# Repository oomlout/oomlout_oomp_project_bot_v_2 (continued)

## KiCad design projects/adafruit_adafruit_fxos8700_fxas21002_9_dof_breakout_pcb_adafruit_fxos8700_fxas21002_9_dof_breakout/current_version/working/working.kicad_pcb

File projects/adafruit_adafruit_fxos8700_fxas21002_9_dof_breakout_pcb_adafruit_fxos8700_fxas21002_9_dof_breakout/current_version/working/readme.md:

# adafruit_fxos8700_fxas21002_9_dof_breakout_pcb
 
## summary 
* id: adafruit_adafruit_fxos8700_fxas21002_9_dof_breakout_pcb_adafruit_fxos8700_fxas21002_9_dof_breakout
* user: adafruit
* name: adafruit_fxos8700_fxas21002_9_dof_breakout_pcb
* board: adafruit_fxos8700_fxas21002_9_dof_breakout
* repo: https://github.com/adafruit/Adafruit-FXOS8700-FXAS21002-9-DoF-Breakout-PCB

* src_file_repo_sch: 
* src_file_repo_sch_link: https://github.com/adafruit/Adafruit-FXOS8700-FXAS21002-9-DoF-Breakout-PCB/tree/master/
* full details link: https://github.com/oomlout/oomlout_oomp_project_bot_v_2/tree/main/projects/adafruit_adafruit_fxos8700_fxas21002_9_dof_breakout_pcb_adafruit_fxos8700_fxas21002_9_dof_breakout/current_version/working  

## schematic  
  
[schematic (pdf)](working_schematic.pdf) 

## pcb  

[board (pdf)](working.pdf)  

## working_bom
| Id | Designator | Footprint | Quantity | Designation | Supplier and ref |  | None | 
| --- | --- | --- | --- | --- | --- | --- | --- | 
| 1 | U$28 | SYMBOL_GYRO_CLOCKWISE | 1 |  |  |  | [''] | 
| 2 | U$27 | SYMBOL_GYRO_CCLOCKWISE | 1 |  |  |  | [''] | 
| 3 | U$1,U$3,U$4,U$2 | MOUNTINGHOLE_2.5_PLATED | 4 | MOUNTINGHOLE2.5 |  |  | [''] | 
| 4 | U1 | SOT23-5 | 1 | MIC5225-3.3V |  |  | [''] | 
| 5 | JP2 | 1X04_ROUND | 1 |  |  |  | [''] | 
| 6 | C2,C3,C7,C5 | 0805-NO | 4 | 0.1uF |  |  | [''] | 
| 7 | C4 | 0805-NO | 1 | 10uF |  |  | [''] | 
| 8 | FID3,FID2,FID1 | FIDUCIAL_1MM | 3 | FIDUCIAL_1MM |  |  | [''] | 
| 9 | JP1 | 1X06_ROUND_70 | 1 |  |  |  | [''] | 
| 10 | R6,R1,R5,R2,R3,R4 | 0805-NO | 6 | 10K |  |  | [''] | 
| 11 | D1 | SOD-323 | 1 | 1N4148 |  |  | [''] | 
| 12 | Q3,Q2,Q1 | SOT23-WIDE | 3 | BSS138 |  |  | [''] | 
| 13 | U$26 | ADAFRUIT_2.5MM | 1 |  |  |  | [''] | 
| 14 | C6,C1 | 0805-NO | 2 | 10ÂµF |  |  | [''] | 
| 15 | U$31 | SYMBOL_GYRO_Z | 1 |  |  |  | [''] | 
| 16 | U2 | QFN16_3MM_FREESCALE_5X3 | 1 | FXOS8700CQ |  |  | [''] | 
| 17 | U4 | QFN24_4MM_FREESCALE_7X5 | 1 | FXAS21002C |  |  | [''] | 
| 18 | U$32 | PCBFEAT-REV-040 | 1 |  |  |  | [''] | 

## bom_schematic
| Ref | Qnty | Value | Cmp name | Footprint | Description | Vendor | DNP | 
| --- | --- | --- | --- | --- | --- | --- | --- | 
| C1, C6 | 2 | 10ÂµF | CAP_CERAMIC0805-NOOUTLINE | working:0805-NO |  |  |  | 
| C2, C3, C5, C7 | 4 | 0.1uF | CAP_CERAMIC0805-NOOUTLINE | working:0805-NO |  |  |  | 
| C4 | 1 | 10uF | CAP_CERAMIC0805-NOOUTLINE | working:0805-NO |  |  |  | 
| D1 | 1 | 1N4148 | DIODESOD-323 | working:SOD-323 |  |  |  | 
| FID1, FID2, FID3 | 3 | FIDUCIAL_1MM | FIDUCIAL_1MM | working:FIDUCIAL_1MM |  |  |  | 
| JP1 | 1 | HEADER-1X670MIL | HEADER-1X670MIL | working:1X06_ROUND_70 |  |  |  | 
| JP2 | 1 | HEADER-1X4ROUND | HEADER-1X4ROUND | working:1X04_ROUND |  |  |  | 
| Q1, Q2, Q3 | 3 | BSS138 | MOSFET-NWIDE | working:SOT23-WIDE |  |  |  | 
| R1, R2, R3, R4, R5, R6 | 6 | 10K | RESISTOR0805_NOOUTLINE | working:0805-NO |  |  |  | 
| U1 | 1 | MIC5225-3.3V | VREG_SOT23-5 | working:SOT23-5 |  |  |  | 
| U2 | 1 | FXOS8700CQ | ACCEL_MAG_FXOS8700CQ | working:QFN16_3MM_FREESCALE_5X3 |  |  |  | 
| U4 | 1 | FXAS21002C | GYRO_FXAS21002C | working:QFN24_4MM_FREESCALE_7X5 |  |  |  | 
| U$1, U$2, U$3, U$4 | 4 | MOUNTINGHOLE2.5 | MOUNTINGHOLE2.5 | working:MOUNTINGHOLE_2.5_PLATED |  |  |  | 

## mounting_holes
| x | y | package | value | ref | size | 
| --- | --- | --- | --- | --- | --- | 
| 22.86 | 0.0 | MOUNTINGHOLE_2.5_PLATED | MOUNTINGHOLE2.5 | U$1 | m3 | 
| 0.0 | 15.24 | MOUNTINGHOLE_2.5_PLATED | MOUNTINGHOLE2.5 | U$2 | m3 | 
| 22.86 | 15.24 | MOUNTINGHOLE_2.5_PLATED | MOUNTINGHOLE2.5 | U$3 | m3 | 
| 0.0 | 0.0 | MOUNTINGHOLE_2.5_PLATED | MOUNTINGHOLE2.5 | U$4 | m3 |

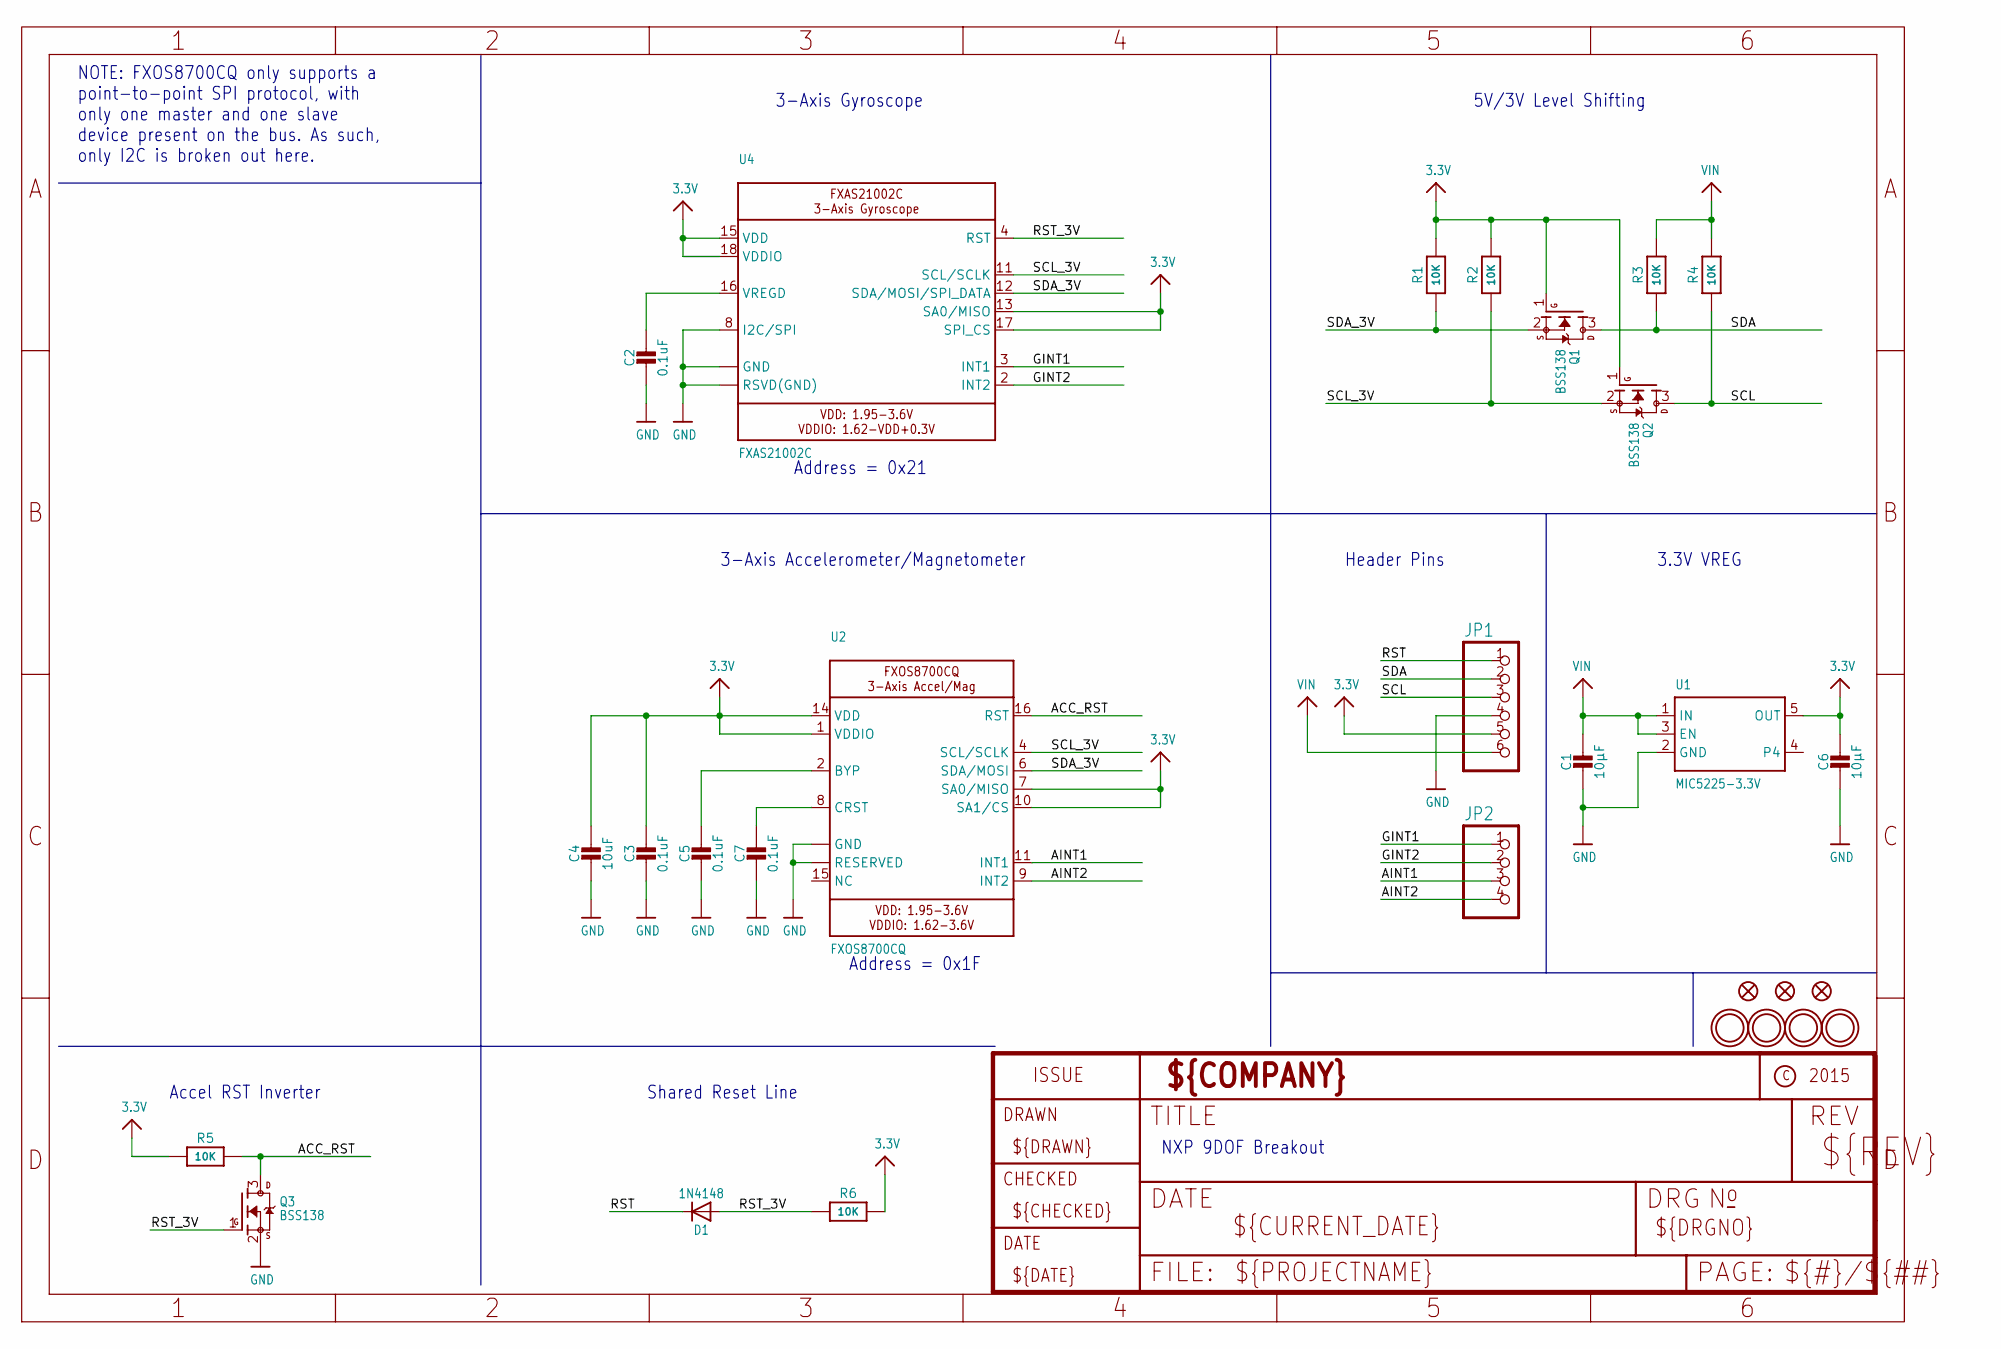
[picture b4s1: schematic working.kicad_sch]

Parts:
C1, C6: 10µF; 0805-NO
C2, C3, C5, C7: 0.1uF; 0805-NO
C4: 10uF; 0805-NO
D1: 1N4148; SOD-323
FID1, FID2, FID3: FIDUCIAL_1MM
JP1: HEADER-1X670MIL; 1X06_ROUND_70
JP2: HEADER-1X4ROUND; 1X04_ROUND
Q1, Q2, Q3: BSS138; SOT23-WIDE
R1, R2, R3, R4, R5, R6: 10K; 0805-NO
U1: MIC5225-3.3V; SOT23-5
U2: FXOS8700CQ; QFN16_3MM_FREESCALE_5X3
U4: FXAS21002C; QFN24_4MM_FREESCALE_7X5
U$1, U$2, U$3, U$4: MOUNTINGHOLE2.5; MOUNTINGHOLE_2.5_PLATED

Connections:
3.3V: C3.1, C4.1, C6.1, JP1.5, Q1.1 (G), Q2.1 (G), R1.2, R2.2, R5.1, R6.2, U1.5 (OUT), U2.1 (VDDIO), U2.7 (SA0/MISO), U2.10 (SA1/CS), U2.14 (VDD), U4.13 (SA0/MISO), U4.15 (VDD), U4.17 (SPI_CS), U4.18 (VDDIO)
ACC_RST: Q3.3 (D), R5.2, U2.16 (RST)
AINT1: JP2.3, U2.11 (INT1)
AINT2: JP2.4, U2.9 (INT2)
GINT1: JP2.1, U4.3 (INT1)
GINT2: JP2.2, U4.2 (INT2)
GND: C1.2, C2.2, C3.2, C4.2, C5.2, C6.2, C7.2, JP1.4, Q3.2 (S), U1.2 (GND), U2.3 (RESERVED), U2.5 (GND), U2.12 (GND), U2.13 (RESERVED), U4.1 (GND), U4.5 (GND), U4.6 (RSVD(GND)), U4.7 (RSVD(GND)), U4.8 (I2C/SPI), U4.9 (RSVD(GND)), U4.10 (RSVD(GND)), U4.14 (GND), U4.19 (GND), U4.20 (RSVD(GND)), U4.21 (RSVD(GND)), U4.22 (RSVD(GND)), U4.23 (RSVD(GND)), U4.24 (RSVD(GND))
unnamed: C2.1, U4.16 (VREGD)
unnamed: C5.1, U2.2 (BYP)
unnamed: C7.1, U2.8 (CRST)
RST: D1.C, JP1.1
RST_3V: D1.A, Q3.1 (G), R6.1, U4.4 (RST)
SCL: JP1.3, Q2.3 (D), R4.1
SCL_3V: Q2.2 (S), R2.1, U2.4 (SCL/SCLK), U4.11 (SCL/SCLK)
SDA: JP1.2, Q1.3 (D), R3.1
SDA_3V: Q1.2 (S), R1.1, U2.6 (SDA/MOSI), U4.12 (SDA/MOSI/SPI_DATA)
VIN: C1.1, JP1.6, R3.2, R4.2, U1.1 (IN), U1.3 (EN)

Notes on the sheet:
Address = 0x21
3-Axis Gyroscope
Address = 0x1F
3-Axis Accelerometer/Magnetometer
Accel RST Inverter
Shared Reset Line
NOTE: FXOS8700CQ only supports a point-to-point SPI protocol, with only one master and one slave device present on the bus. As such, only I2C is broken out here.
Header Pins
5V/3V Level Shifting
NXP 9DOF Breakout
3.3V VREG

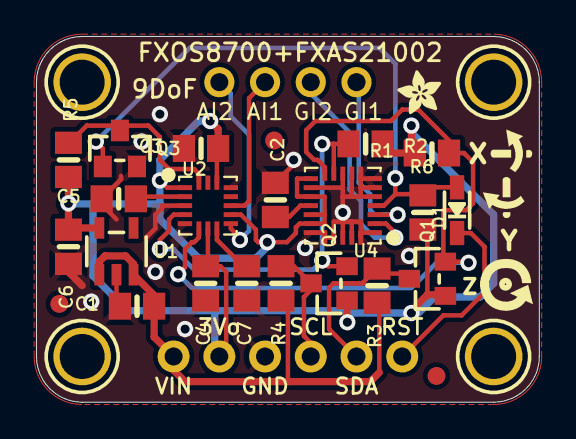
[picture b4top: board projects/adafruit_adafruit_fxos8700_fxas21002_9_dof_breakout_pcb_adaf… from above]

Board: 2 copper layers, 27.9 x 20.3 mm, 34 parts (1 on the bottom side), 17 nets.

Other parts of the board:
U$26: ADAFRUIT_2.5MM
U$27: SYMBOL_GYRO_CCLOCKWISE
U$28: SYMBOL_GYRO_CLOCKWISE
U$31: SYMBOL_GYRO_Z
U$32: PCBFEAT-REV-040

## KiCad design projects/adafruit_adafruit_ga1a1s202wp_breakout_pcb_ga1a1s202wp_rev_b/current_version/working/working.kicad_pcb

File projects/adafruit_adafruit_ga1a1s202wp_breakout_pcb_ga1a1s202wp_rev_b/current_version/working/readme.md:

# adafruit_ga1a1s202wp_breakout_pcb
 
## summary 
* id: adafruit_adafruit_ga1a1s202wp_breakout_pcb_ga1a1s202wp_rev_b
* user: adafruit
* name: adafruit_ga1a1s202wp_breakout_pcb
* board: ga1a1s202wp_rev_b
* repo: https://github.com/adafruit/Adafruit-GA1A1S202WP-Breakout-PCB

* src_file_repo_sch: 
* src_file_repo_sch_link: https://github.com/adafruit/Adafruit-GA1A1S202WP-Breakout-PCB/tree/master/
* full details link: https://github.com/oomlout/oomlout_oomp_project_bot_v_2/tree/main/projects/adafruit_adafruit_ga1a1s202wp_breakout_pcb_ga1a1s202wp_rev_b/current_version/working  

## schematic  
  
[schematic (pdf)](working_schematic.pdf) 

## pcb  

[board (pdf)](working.pdf)  

## working_bom
| Id | Designator | Footprint | Quantity | Designation | Supplier and ref |  | None | 
| --- | --- | --- | --- | --- | --- | --- | --- | 
| 1 | FID1,FID2 | FIDUCIAL_1MM | 2 | FIDUCIAL" |  |  | [''] | 
| 2 | U$3 | MOUNTINGHOLE_2.5_PLATED | 1 | MOUNTINGHOLE2.5 |  |  | [''] | 
| 3 | U$4 | ADAFRUIT_2.5MM | 1 |  |  |  | [''] | 
| 4 | C1 | _0805MP | 1 | 0.1uF |  |  | [''] | 
| 5 | JP1 | 1X03_ROUND | 1 |  |  |  | [''] | 
| 6 | U1 | GA1A1S202WP | 1 | GA1A1S202WP |  |  | [''] | 
| 7 | R1 | _0805MP | 1 | 68K |  |  | [''] | 

## bom_schematic
| Ref | Qnty | Value | Cmp name | Footprint | Description | Vendor | DNP | 
| --- | --- | --- | --- | --- | --- | --- | --- | 
| C1 | 1 | 0.1uF | CAP_CERAMIC_0805MP | working:_0805MP |  |  |  | 
| FID1, FID2 | 2 | FIDUCIAL"" | FIDUCIAL{dblquote}{dblquote} | working:FIDUCIAL_1MM |  |  |  | 
| JP1 | 1 | HEADER-1X3ROUND | HEADER-1X3ROUND | working:1X03_ROUND |  |  |  | 
| R1 | 1 | 68K | RESISTOR_0805MP | working:_0805MP |  |  |  | 
| U1 | 1 | GA1A1S202WP | GA1A1S202WP | working:GA1A1S202WP |  |  |  | 
| U$3 | 1 | MOUNTINGHOLE2.5 | MOUNTINGHOLE2.5 | working:MOUNTINGHOLE_2.5_PLATED |  |  |  | 

## mounting_holes
| x | y | package | value | ref | size | 
| --- | --- | --- | --- | --- | --- | 
| 0.0 | 0.0 | MOUNTINGHOLE_2.5_PLATED | MOUNTINGHOLE2.5 | U$3 | m3 |

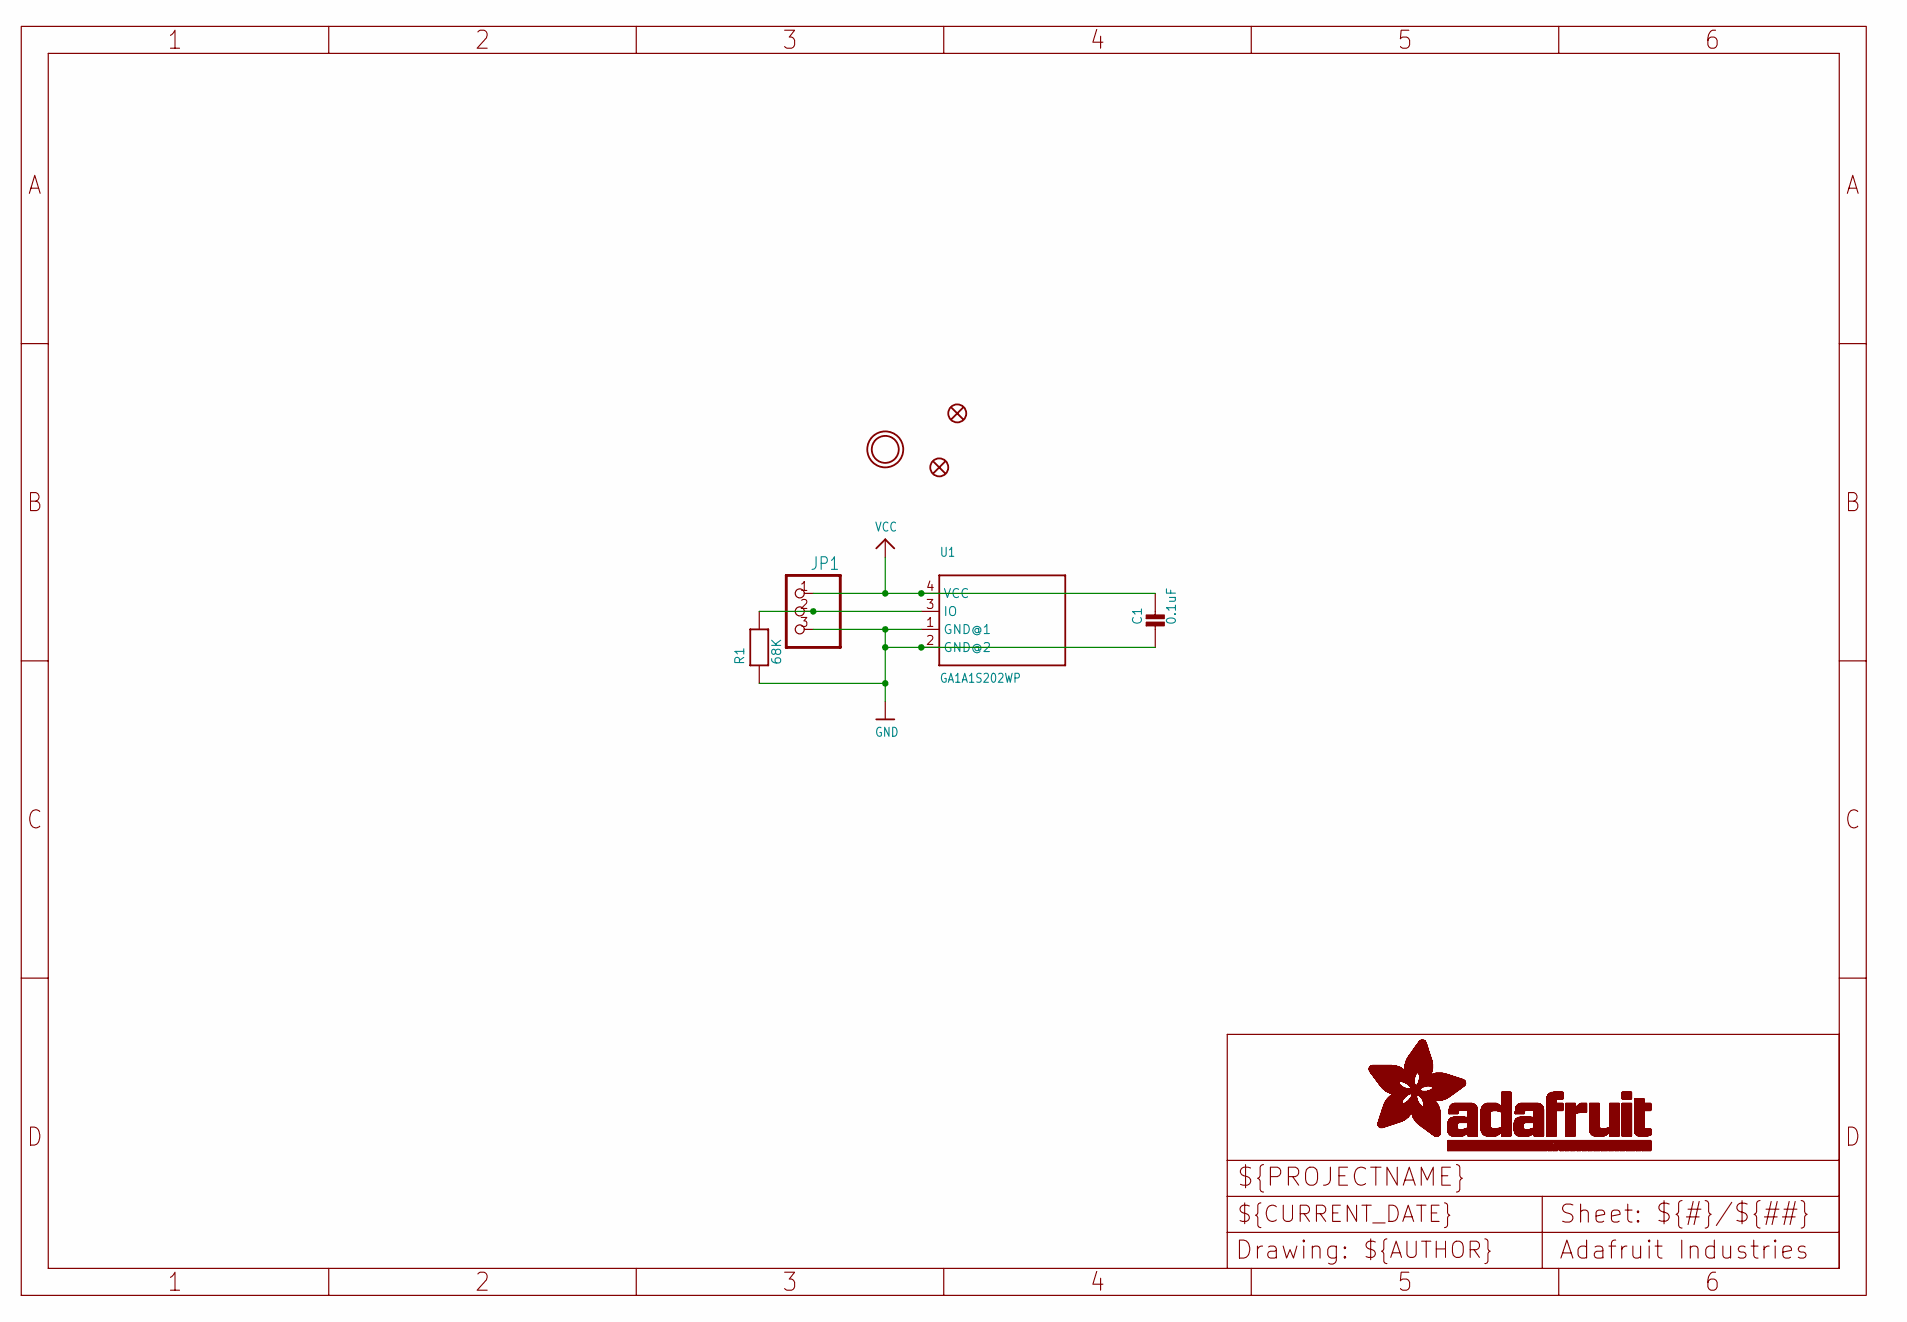
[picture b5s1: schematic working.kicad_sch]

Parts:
C1: 0.1uF; _0805MP
FID1, FID2: FIDUCIAL""; FIDUCIAL_1MM
JP1: HEADER-1X3ROUND; 1X03_ROUND
R1: 68K; _0805MP
U1: GA1A1S202WP
U$3: MOUNTINGHOLE2.5; MOUNTINGHOLE_2.5_PLATED

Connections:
GND: C1.2, JP1.3, R1.1, U1.1 (GND@1), U1.2 (GND@2)
unnamed: JP1.2, R1.2, U1.3 (IO)
VCC: C1.1, JP1.1, U1.4 (VCC)

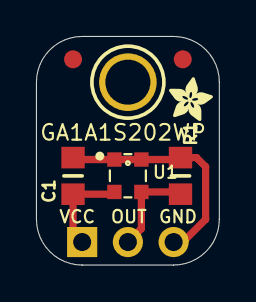
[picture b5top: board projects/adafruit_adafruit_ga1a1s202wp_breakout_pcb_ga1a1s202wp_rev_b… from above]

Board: 2 copper layers, 10.2 x 12.7 mm, 8 parts (0 on the bottom side), 3 nets.

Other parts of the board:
U$4: ADAFRUIT_2.5MM

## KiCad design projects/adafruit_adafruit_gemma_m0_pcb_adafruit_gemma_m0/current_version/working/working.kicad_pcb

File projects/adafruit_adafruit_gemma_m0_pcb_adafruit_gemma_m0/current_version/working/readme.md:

# adafruit_gemma_m0_pcb
 
## summary 
* id: adafruit_adafruit_gemma_m0_pcb_adafruit_gemma_m0
* user: adafruit
* name: adafruit_gemma_m0_pcb
* board: adafruit_gemma_m0
* repo: https://github.com/adafruit/Adafruit-Gemma-M0-PCB

* src_file_repo_sch: 
* src_file_repo_sch_link: https://github.com/adafruit/Adafruit-Gemma-M0-PCB/tree/master/
* full details link: https://github.com/oomlout/oomlout_oomp_project_bot_v_2/tree/main/projects/adafruit_adafruit_gemma_m0_pcb_adafruit_gemma_m0/current_version/working  

## schematic  
  
[schematic (pdf)](working_schematic.pdf) 

## pcb  

[board (pdf)](working.pdf)  

## working_bom
| Id | Designator | Footprint | Quantity | Designation | Supplier and ref |  | None | 
| --- | --- | --- | --- | --- | --- | --- | --- | 
| 1 | GND0,UNK3V3,B1,B2,B0,VBAT0 | SEWALLI | 6 | SEWTAP-ALLIGATOR |  |  | [''] | 
| 2 | SW1 | EG1390 | 1 | EG1218 |  |  | [''] | 
| 3 | U$1,U$6 | FIDUCIAL_1MM | 2 | FIDUCIAL_1MM |  |  | [''] | 
| 4 | C2,C3 | 0603-NO | 2 | 1uF |  |  | [''] | 
| 5 | C8,C1 | 0805-NO | 2 | 10uF |  |  | [''] | 
| 6 | D1,D2 | SOD-123FL | 2 | SCHOTTKY |  |  | [''] | 
| 7 | R5 | 0603-NO | 1 | 1K |  |  | [''] | 
| 8 | PWR0 | CHIPLED_0603_NOOUTLINE | 1 | red |  |  | [''] | 
| 9 | CN1 | JSTPH2 | 1 | JST-PH |  |  | [''] | 
| 10 | LED1 | APA102_2020 | 1 | AP102-2020 |  |  | [''] | 
| 11 | IC1 | QFN32_5MM | 1 | ATSAMD21E |  |  | [''] | 
| 12 | Q1 | BTN_KMR2_4.6X2.8 | 1 | reset |  |  | [''] | 
| 13 | X2 | 4UCONN_20329_V2 | 1 | MicroUSB |  |  | [''] | 
| 14 | U$8 | GEMMA_M0_TOP | 1 |  |  |  | [''] | 
| 15 | U1 | SOT23-5 | 1 | AP2112K-3.3 |  |  | [''] | 
| 16 | TP1 | TP16R | 1 | TPTP16R |  |  | [''] | 
| 17 | SWD0,SWC0 | TP15R | 2 | TPTP15R |  |  | [''] | 
| 18 | U$10 | PCBFEAT-REV-040 | 1 |  |  |  | [''] | 
| 19 | U$7 | GEMMA_M0_BOTTOM | 1 |  |  |  | [''] | 

## bom_schematic
| Ref | Qnty | Value | Cmp name | Footprint | Description | Vendor | DNP | 
| --- | --- | --- | --- | --- | --- | --- | --- | 
| B0, B1, B2 | 3 | SEWTAP-ALLIGATOR | SEWTAP-ALLIGATOR | working:SEWALLI |  |  |  | 
| C1, C8 | 2 | 10uF | CAP_CERAMIC0805-NOOUTLINE | working:0805-NO |  |  |  | 
| C2, C3 | 2 | 1uF | CAP_CERAMIC0603_NO | working:0603-NO |  |  |  | 
| CN1 | 1 | JST-PH | CON_JST_PH_2PIN | working:JSTPH2 |  |  |  | 
| D1, D2 | 2 | SCHOTTKY | DIODE_SOD-123FL | working:SOD-123FL |  |  |  | 
| GND0 | 1 | SEWTAP-ALLIGATOR | SEWTAP-ALLIGATOR | working:SEWALLI |  |  |  | 
| IC1 | 1 | ATSAMD21E | ATSAMD21E | working:QFN32_5MM |  |  |  | 
| LED1 | 1 | AP102-2020 | APA1022020 | working:APA102_2020 |  |  |  | 
| PWR0 | 1 | red | LED0603_NOOUTLINE | working:CHIPLED_0603_NOOUTLINE |  |  |  | 
| Q1 | 1 | reset | SWITCH_TACT_SMT4.6X2.8 | working:BTN_KMR2_4.6X2.8 |  |  |  | 
| R5 | 1 | 1K | RESISTOR_0603_NOOUT | working:0603-NO |  |  |  | 
| SW1 | 1 | EG1218 | SWITCH_DPDTEG1390 | working:EG1390 |  |  |  | 
| SWC0 | 1 | TPTP15R | TPTP15R | working:TP15R |  |  |  | 
| SWD0 | 1 | TPTP15R | TPTP15R | working:TP15R |  |  |  | 
| TP1 | 1 | TPTP16R | TPTP16R | working:TP16R |  |  |  | 
| U1 | 1 | AP2112K-3.3 | VREG_SOT23-5 | working:SOT23-5 |  |  |  | 
| U$1, U$6 | 2 | FIDUCIAL_1MM | FIDUCIAL_1MM | working:FIDUCIAL_1MM |  |  |  | 
| UNK3V3 | 1 | SEWTAP-ALLIGATOR | SEWTAP-ALLIGATOR | working:SEWALLI |  |  |  | 
| VBAT0 | 1 | SEWTAP-ALLIGATOR | SEWTAP-ALLIGATOR | working:SEWALLI |  |  |  | 
| X2 | 1 | MicroUSB | USB_MICRO_20329_V2 | working:4UCONN_20329_V2 |  |  |  |

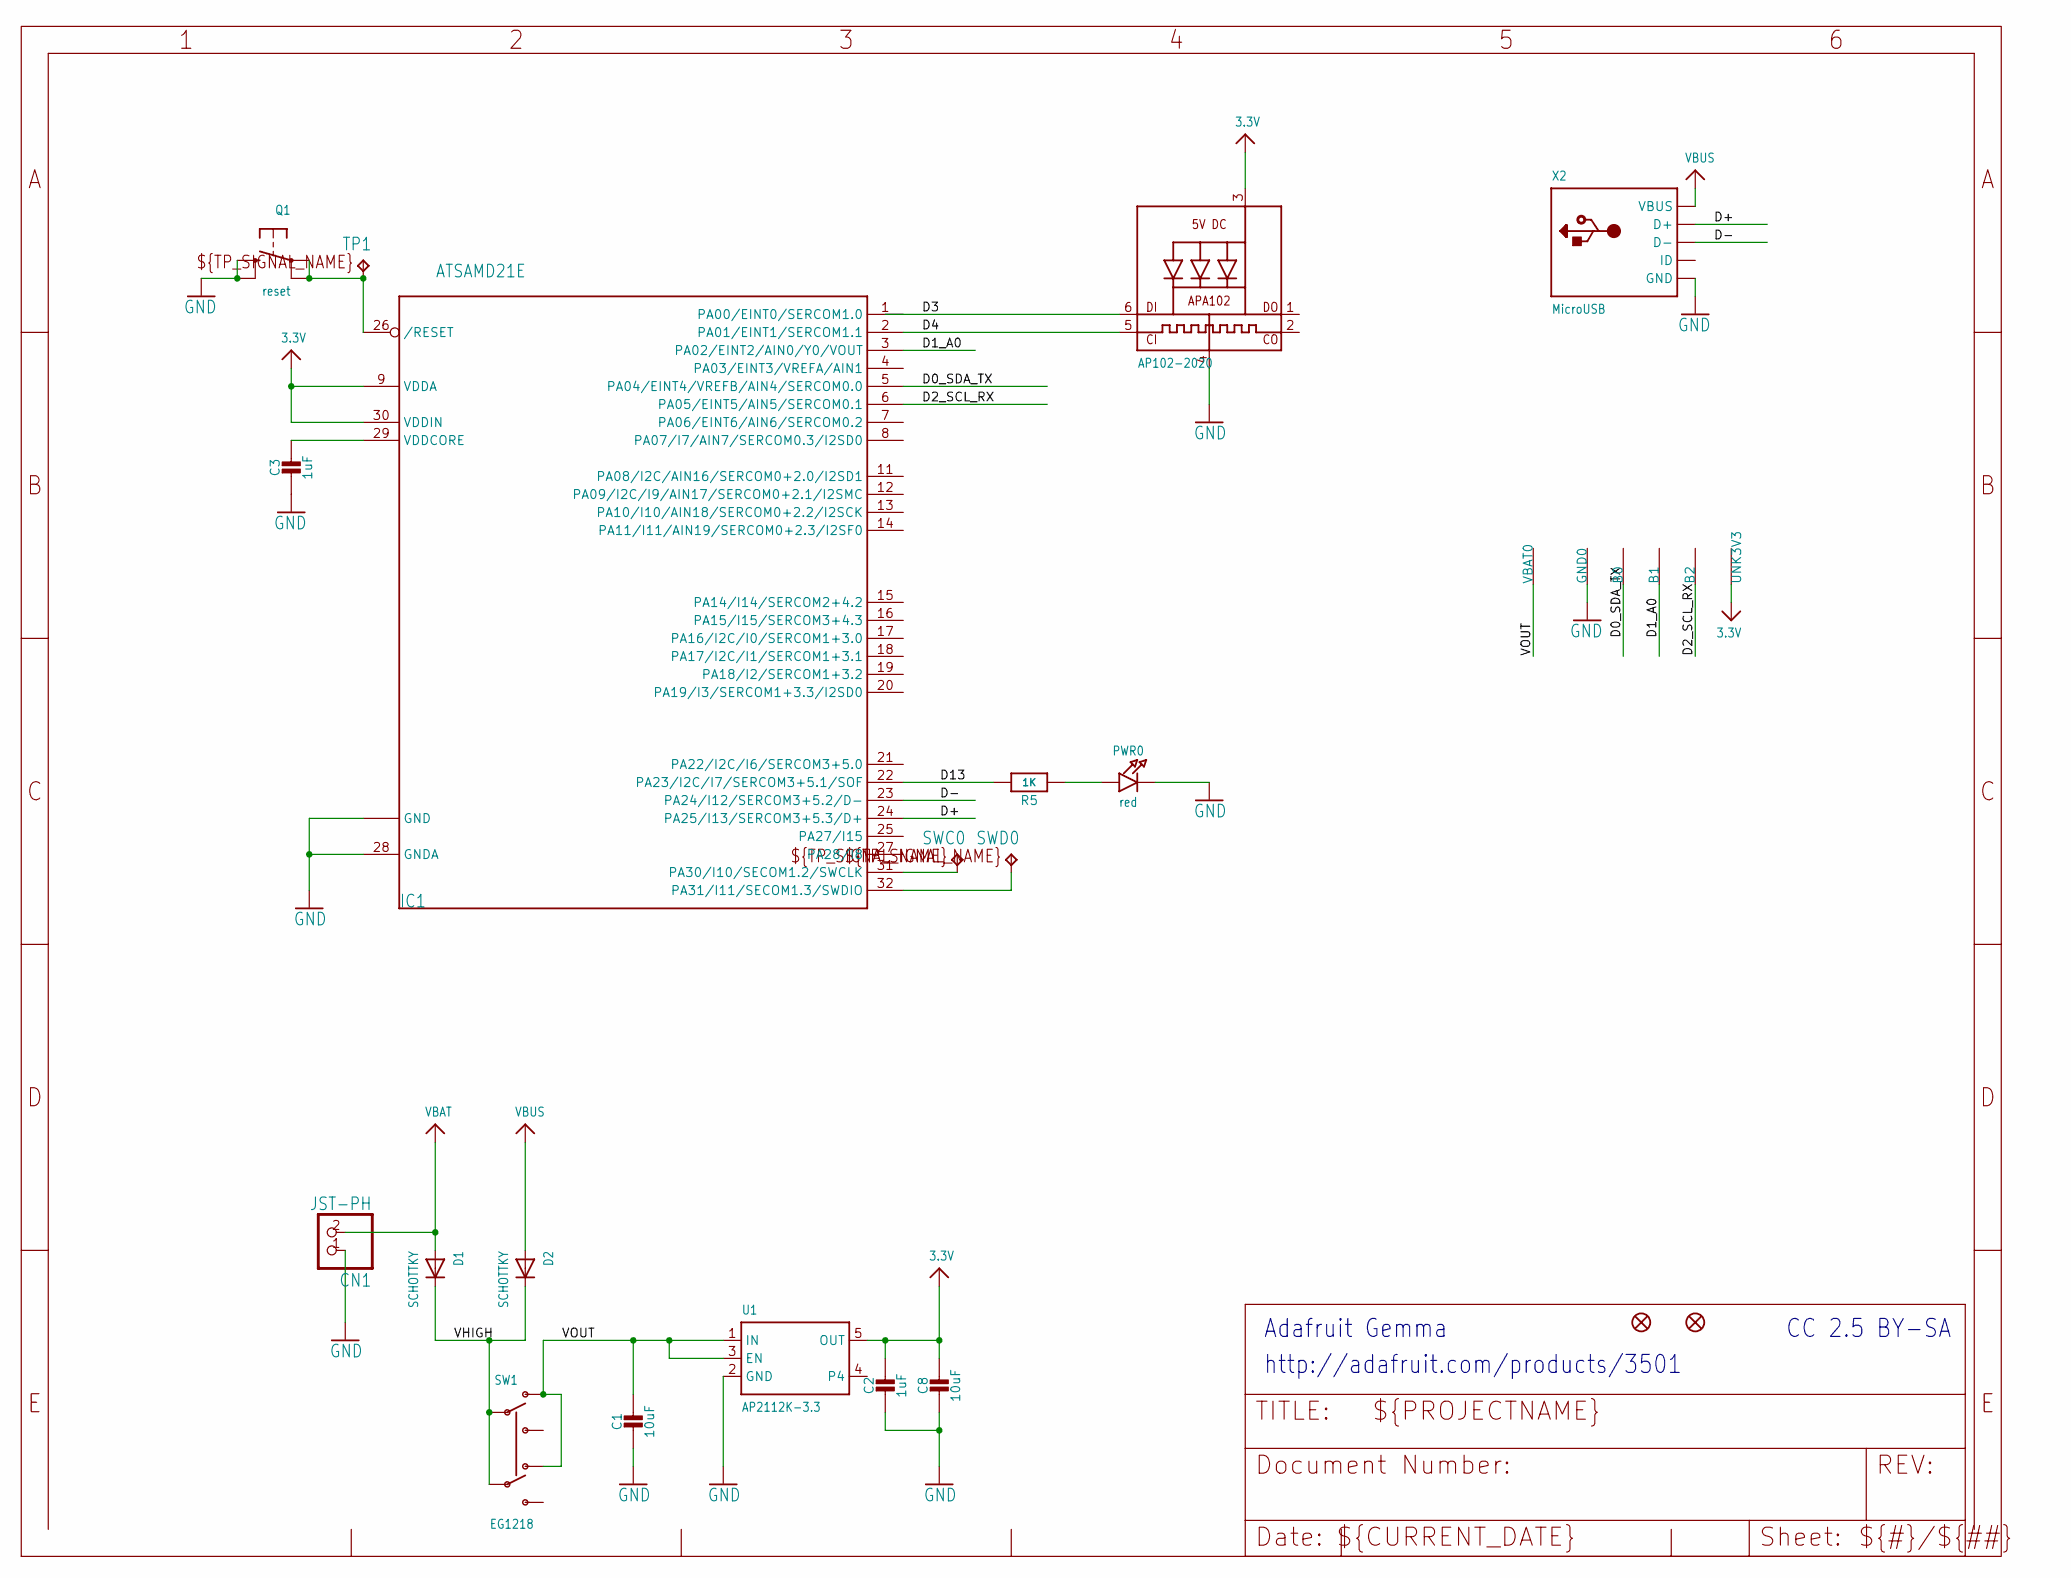
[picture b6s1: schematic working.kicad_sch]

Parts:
B0, B1, B2: SEWTAP-ALLIGATOR; SEWALLI
C1, C8: 10uF; 0805-NO
C2, C3: 1uF; 0603-NO
CN1: JST-PH; JSTPH2
D1, D2: SCHOTTKY; SOD-123FL
GND0: SEWTAP-ALLIGATOR; SEWALLI
IC1: ATSAMD21E; QFN32_5MM
LED1: AP102-2020; APA102_2020
PWR0: red; CHIPLED_0603_NOOUTLINE
Q1: reset; BTN_KMR2_4.6X2.8
R5: 1K; 0603-NO
SW1: EG1218; EG1390
SWC0: TPTP15R; TP15R
SWD0: TPTP15R; TP15R
TP1: TPTP16R; TP16R
U1: AP2112K-3.3; SOT23-5
U$1, U$6: FIDUCIAL_1MM
UNK3V3: SEWTAP-ALLIGATOR; SEWALLI
VBAT0: SEWTAP-ALLIGATOR; SEWALLI
X2: MicroUSB; 4UCONN_20329_V2

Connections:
3.3V: C2.1, C8.1, IC1.9 (VDDA), IC1.30 (VDDIN), LED1.3 (VDD), U1.5 (OUT), UNK3V3.P$1
D0_SDA_TX: B0.P$1, IC1.5 (PA04/EINT4/VREFB/AIN4/SERCOM0.0)
D1_A0: B1.P$1, IC1.3 (PA02/EINT2/AIN0/Y0/VOUT)
D2_SCL_RX: B2.P$1, IC1.6 (PA05/EINT5/AIN5/SERCOM0.1)
D3: IC1.1 (PA00/EINT0/SERCOM1.0), LED1.6 (DI)
D4: IC1.2 (PA01/EINT1/SERCOM1.1), LED1.5 (CKI)
D13: IC1.22 (PA23/I2C/I7/SERCOM3+5.1/SOF), R5.2
D+: IC1.24 (PA25/I13/SERCOM3+5.3/D+), X2.D+
D-: IC1.23 (PA24/I12/SERCOM3+5.2/D-), X2.D-
GND: C1.2, C2.2, C3.2, C8.2, CN1.1, GND0.P$1, IC1.10 (GND), IC1.28 (GNDA), IC1.33 (GND), LED1.4 (GND), PWR0.C, Q1.B (S), Q1.B' (S1), U1.2 (GND), X2.BASE@1 (GND), X2.BASE@2 (GND), X2.GND, X2.SPRT@1 (GND), X2.SPRT@2 (GND), X2.SPRT@3 (GND), X2.SPRT@4 (GND)
unnamed: PWR0.A, R5.1
SWCLK: IC1.31 (PA30/I10/SECOM1.2/SWCLK), SWC0.TP
SWDIO: IC1.32 (PA31/I11/SECOM1.3/SWDIO), SWD0.TP
VBAT: CN1.2, D1.A
VBUS: D2.A, X2.VBUS
VDDCORE: C3.1, IC1.29 (VDDCORE)
VHIGH: D1.C, D2.C, SW1.P1, SW1.P2
VOUT: C1.1, SW1.O1, SW1.O2, U1.1 (IN), U1.3 (EN), VBAT0.P$1
~RESET: IC1.26 (/RESET), Q1.A, Q1.A' (P1), TP1.TP

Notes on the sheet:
Adafruit Gemma
http://adafruit.com/products/3501
CC 2.5 BY-SA

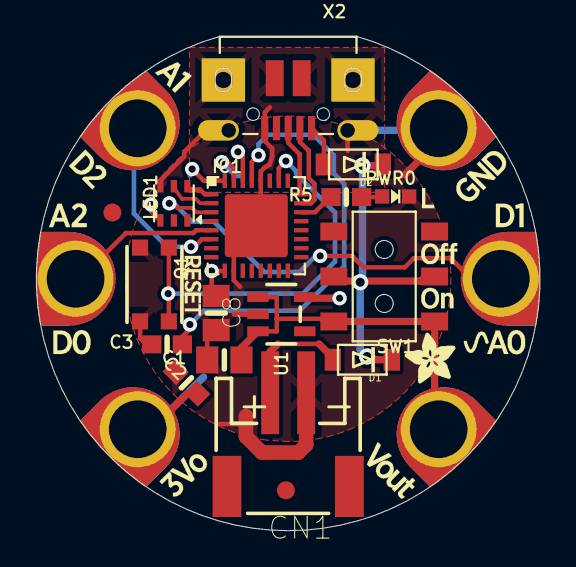
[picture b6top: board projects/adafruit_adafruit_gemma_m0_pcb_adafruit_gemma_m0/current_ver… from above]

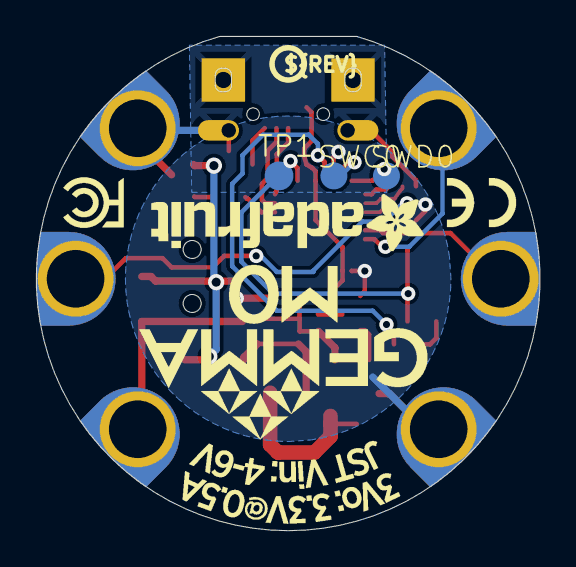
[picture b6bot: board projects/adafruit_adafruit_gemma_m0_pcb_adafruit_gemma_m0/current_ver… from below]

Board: 16 copper layers, 28.0 x 27.5 mm, 29 parts (5 on the bottom side), 19 nets.

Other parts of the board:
U$7: GEMMA_M0_BOTTOM
U$8: GEMMA_M0_TOP
U$10: PCBFEAT-REV-040
